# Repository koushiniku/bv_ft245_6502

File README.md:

# replACIA USB to W65xx Bus Adapter

*This board is still in development.*

This is a replacement for a number of "serial port" solutions for
W65Cxx-based breadboard computers requiring either the W65C51N ACIA or
custom logic and either a MAX232 and DB9 connector or breakout board with
a serial-to-USB or parallel-to-USB chip.

This solution replaces all that on a single board with a FTDI FT245R (aka.
USB Blaster) chip and some logic ICs, all on a 8x5 DIP16 board, which is
smaller than the 14x6 DIP28 ACIA. The board supports USB2.0 with vertical
USB.C connector.

## Pin List

Pin | Name | Type | Description
--- | ---- | ---- | -----------
1 | &phiv;2 | Input | PHI2: The system clock.
2 | CS# | Input | Chip Select from the address decode logic.
3 | R/W# | Input | RWB signal from the CPU.
4 | GND | Power Input | Ground.
5 | V<sub>CC</sub> | Power Input | +5V DC. (+3.3V is unsupported without adding a 12 MHz crystal or upgrading to FT245RN.)
6 | A0 | Input | Address bit 0 from the CPU.
7 | IRQ# | Open Drain Output | Interrupt to the CPU indicating received data is ready to be read. (If you prefer a push-pull interrupt output, replace the 74LVC1G38 with a 74LVC1G00.)
8 | RES# | Input | RESB reset signal from the CPU. This clears the interrupt enable register.
9&ndash;16 | D0&ndash;D7 | Input/Output | The CPU data bus.

## Register 0 &mdash; CSR

Bit | Name | Type | Description
--- | ---- | ---- | -----------
7 | TXE# | Read-Only | If cleared to 0, the transmit buffer is empty and ready to be written to. (Yes, it actually works!)
6 | RXF# | Read-Only | If cleared to 0, the receive buffer is full and has data ready to be read from.
5 | PWREN# | Read-Only | This is the status of the PWREN# signal from the FT245R. If cleared to 0, the device has been configured by USB. If set to 1, the device is in USB suspend mode. This can be used by software as indicating something similar to DSR#.
4 | VBUS | Read-Only | This is the status of USB power. If set to 1, USB is powered, indicating the remote host should be resent. If cleared to 0, the FT245RN device is in reset. This can be used by software as something similar to DCD#.
3:1 | Reserved | Unused |
0 | IRQ_EN | Read/Write | Set to 1 to enable the receive interrupt. The default reset value is 0 (disabled). There is no transmit interrupt; I assumed USB is fast enough that polling TXE# is sufficient. (The ACIA oddly enables the receive interrupt by default.)

## Register 1 &mdash; DATA

When receive data is present, reading from this register returns a byte of
data received from the remote host. This also clears the IRQ (if it was
enabled). When the transmit buffer is empty, writing to this register
transmits a byte of data to the remote host.

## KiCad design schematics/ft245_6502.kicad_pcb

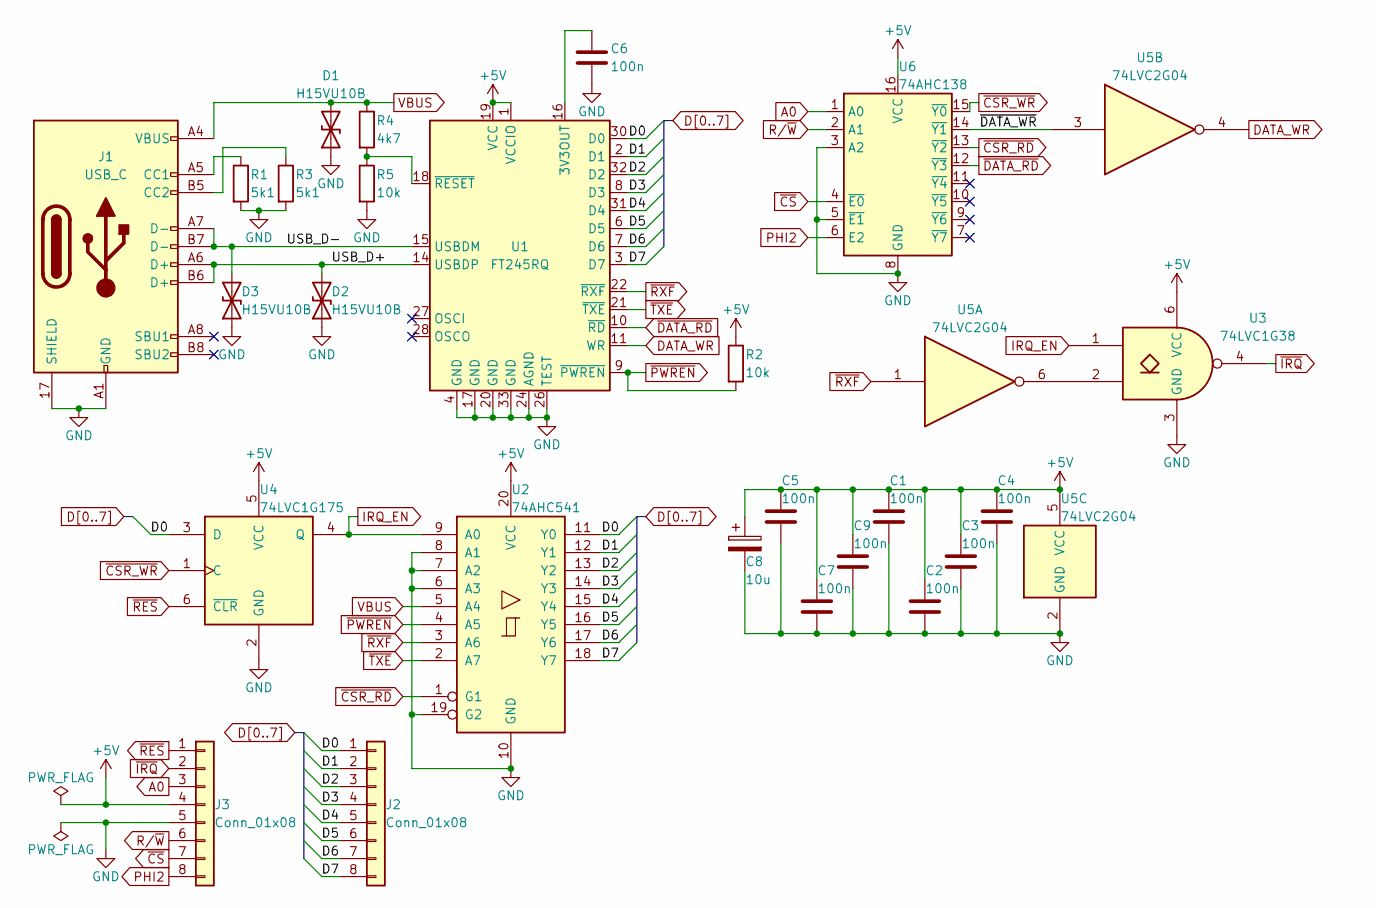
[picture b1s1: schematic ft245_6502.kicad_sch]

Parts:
C1, C2, C3, C4, C5, C6, C7, C9: 100n; CL05B104KO5NNNC; LCSC C1525
C8: 10u; TAJA106K016RNJ; LCSC C7171
D1, D2, D3: H15VU10B; LCSC C20615792
J1: USB_C; TYPE-C-16PLT6_8H-4PC-WT; LCSC C53059472
J2, J3: Conn_01x08; PinHeader_1x08_P2.54mm_Vertical
R1, R3: 5k1; 0402WGF5101TCE; LCSC C25905
R2, R5: 10k; 0402WGF1002TCE; LCSC C25744
R4: 4k7; 0402WGF4701TCE; LCSC C25900
U1: FT245RQ; FT245RQ-TRAY; LCSC C1550574
U2: 74AHC541; 74AHC541BQ-Q100X; LCSC C554414
U3: 74LVC1G38; EM74LVC1G38GM; LCSC C54929569
U4: 74LVC1G175; 74LVC1G175GM_115; LCSC C548286
U5: 74LVC2G04; 74LVC2G04GM_115; LCSC C426707
U6: 74AHC138; 74AHC138BQ_115; LCSC C554237

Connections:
+5V: C1.1, C2.1, C3.1, C4.1, C5.1, C7.1, C8.1, C9.1, J3.4, R2.1, U1.1 (VCCIO), U1.19 (VCC), U2.20 (VCC), U3.6 (VCC), U4.5 (VCC), U5.5 (VCC), U6.16 (VCC)
/USB_D+: D2.2 (A2), J1.A6 (D+), J1.B6 (D+), U1.14 (USBDP)
/USB_D-: D3.2 (A2), J1.A7 (D-), J1.B7 (D-), U1.15 (USBDM)
/~DATA_WR: U5.3, U6.14 (~Y1)
A0: J3.3, U6.1 (A0)
D0: J2.1, U1.30 (D0), U2.11 (Y0), U4.3 (D)
D1: J2.2, U1.2 (D1), U2.12 (Y1)
D2: J2.3, U1.32 (D2), U2.13 (Y2)
D3: J2.4, U1.8 (D3), U2.14 (Y3)
D4: J2.5, U1.31 (D4), U2.15 (Y4)
D5: J2.6, U1.6 (D5), U2.16 (Y5)
D6: J2.7, U1.7 (D6), U2.17 (Y6)
D7: J2.8, U1.3 (D7), U2.18 (Y7)
DATA_WR: U1.11 (WR), U5.4
GND: C1.2, C2.2, C3.2, C4.2, C5.2, C6.2, C7.2, C8.2, C9.2, D1.1 (A1), D2.1 (A1), D3.1 (A1), J1.17 (SHIELD), J1.18 (SHIELD), J1.19 (SHIELD), J1.20 (SHIELD), J1.A1 (GND), J1.A12 (GND), J1.B1 (GND), J1.B12 (GND), J3.5, R1.2, R3.2, R5.2, U1.4 (GND), U1.17 (GND), U1.20 (GND), U1.24 (AGND), U1.26 (TEST), U1.33 (GND), U2.6 (A3), U2.7 (A2), U2.8 (A1), U2.10 (GND), U2.19 (G2), U2.21 (GND), U3.3 (GND), U4.2 (GND), U5.2 (GND), U6.3 (A2), U6.5 (~E1), U6.8 (GND), U6.17 (GND)
IRQ_EN: U2.9 (A0), U3.1, U4.4 (Q)
unnamed: J1.A5 (CC1), R1.1
unnamed: J1.B5 (CC2), R3.1
unnamed: C6.1, U1.16 (3V3OUT)
unnamed: R4.2, R5.1, U1.18 (~RESET)
unnamed: U3.2, U5.6
PHI2: J3.8, U6.6 (E2)
R/~W: J3.6, U6.2 (A1)
VBUS: D1.2 (A2), J1.A4 (VBUS), J1.A9 (VBUS), J1.B4 (VBUS), J1.B9 (VBUS), R4.1, U2.5 (A4)
~CSR_RD: U2.1 (G1), U6.13 (~Y2)
~CSR_WR: U4.1 (C), U6.15 (~Y0)
~CS: J3.7, U6.4 (~E0)
~DATA_RD: U1.10 (~RD), U6.12 (~Y3)
~IRQ: J3.2, U3.4
~PWREN: R2.2, U1.9 (~PWREN), U2.4 (A5)
~RES: J3.1, U4.6 (~CLR)
~RXF: U1.22 (~RXF), U2.3 (A6), U5.1
~TXE: U1.21 (~TXE), U2.2 (A7)

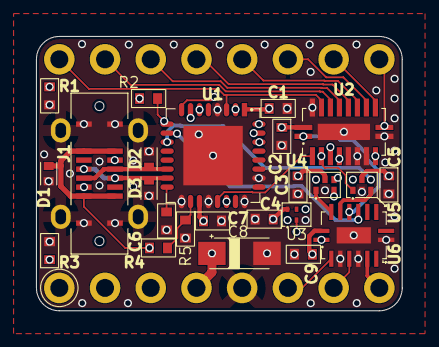
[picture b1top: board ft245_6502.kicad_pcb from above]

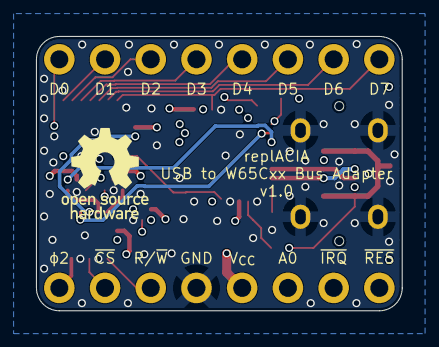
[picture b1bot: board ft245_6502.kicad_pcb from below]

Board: 6 copper layers, 20.3 x 15.2 mm, 26 parts (2 on the bottom side), 33 nets.
